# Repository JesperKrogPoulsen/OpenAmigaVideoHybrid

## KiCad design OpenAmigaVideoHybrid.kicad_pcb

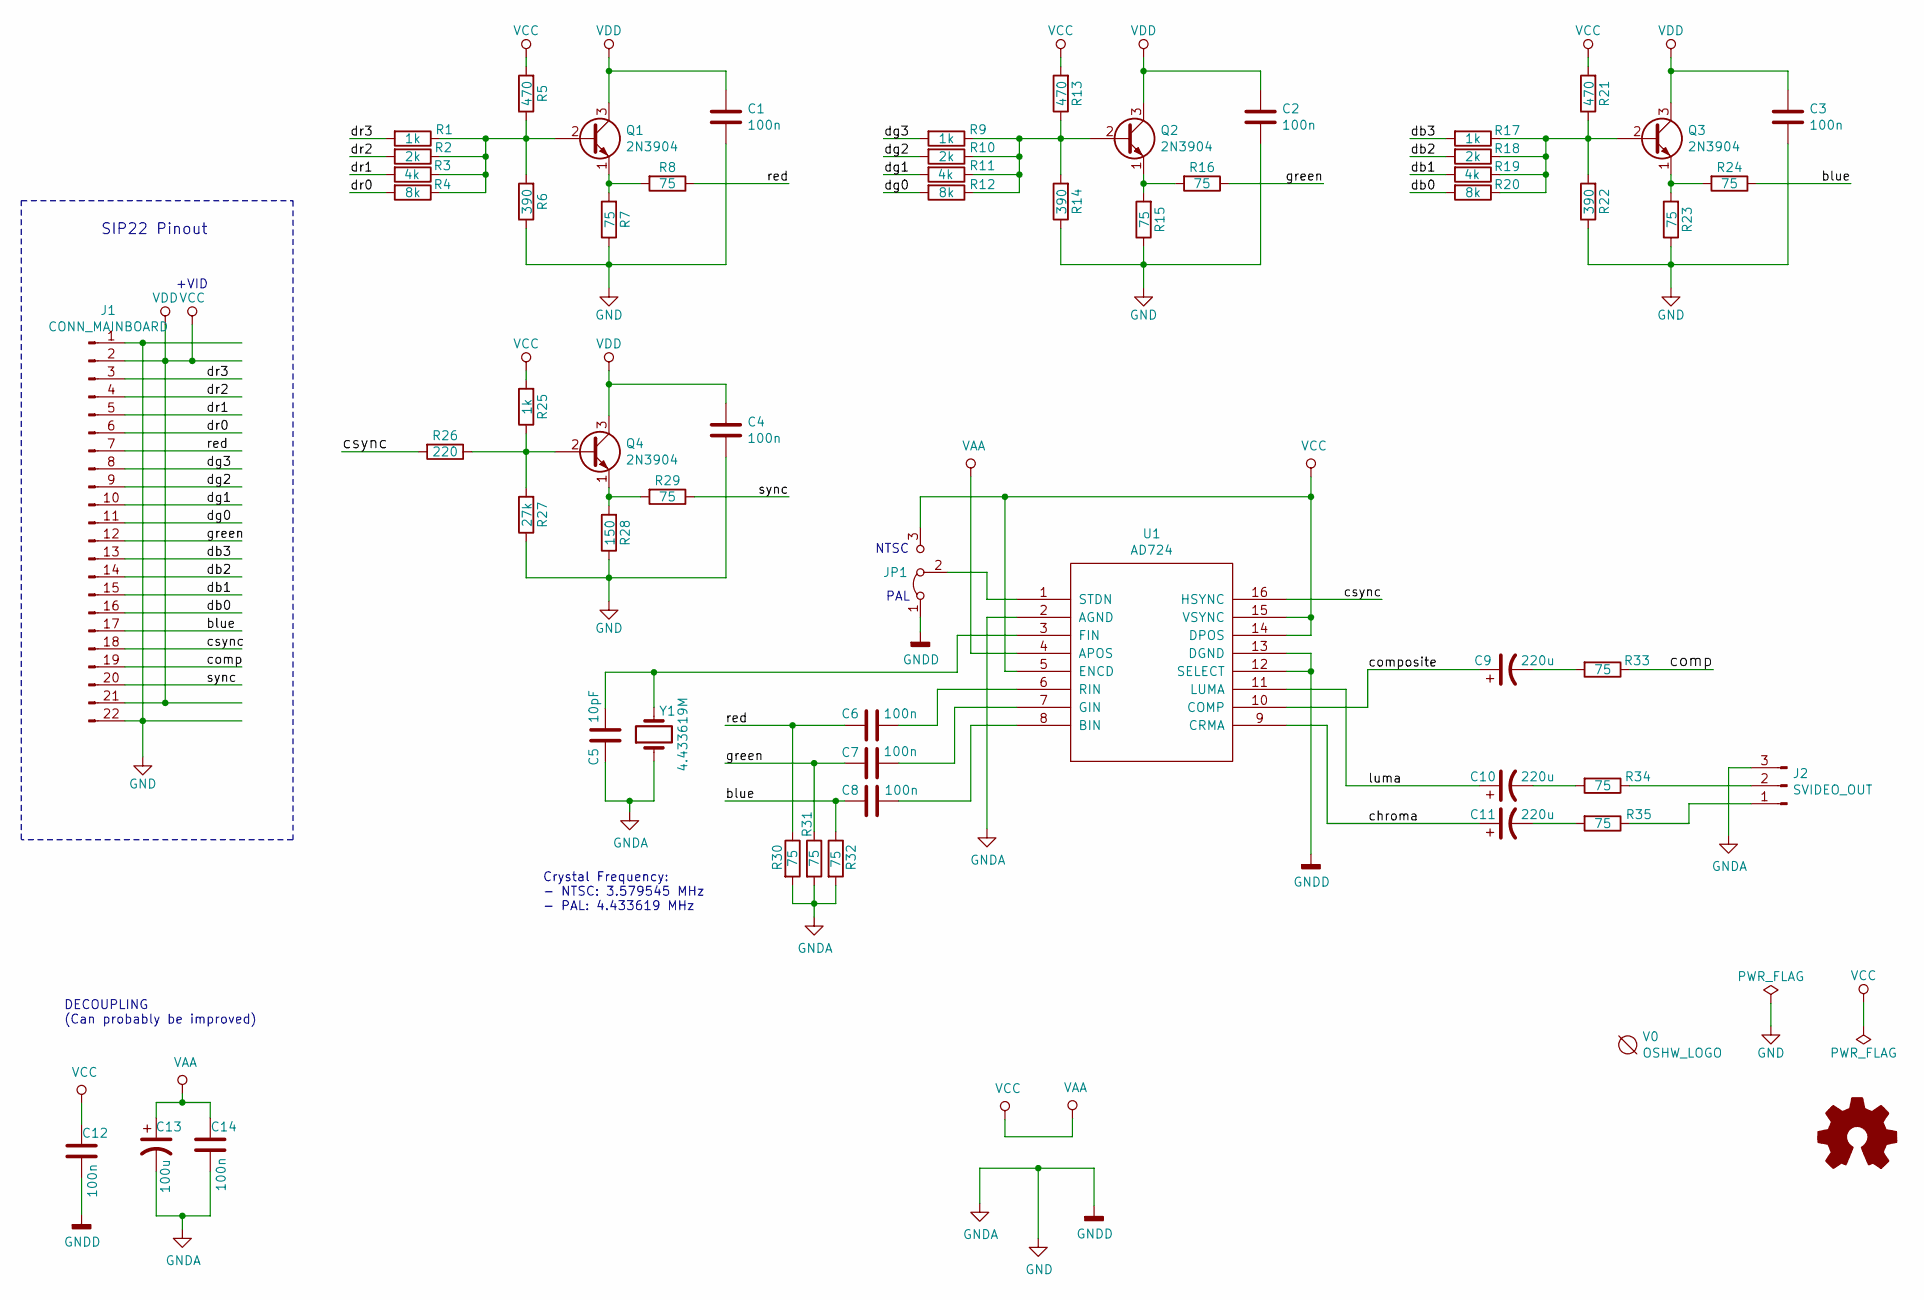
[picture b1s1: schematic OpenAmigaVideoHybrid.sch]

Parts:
C1, C2, C3, C4, C6, C7, C8, C12: 100n; C_0805_2012Metric_Pad1.15x1.40mm_HandSolder
C5: 10pF; C_0805_2012Metric_Pad1.15x1.40mm_HandSolder
C9, C10, C11: 220u; CP_Elec_6.3x7.7
C13: 100u; CP_Elec_6.3x5.8
C14: 100n; C_1206_3216Metric_Pad1.42x1.75mm_HandSolder
J1: CONN_MAINBOARD; PinHeader_1x22_P2.54mm_Vertical
J2: SVIDEO_OUT; Pin_Header_Straight_1x03-ModSilkS
JP1: NTSC/~PAL; SolderJumper-3_P1.3mm_Bridged12_RoundedPad1.0x1.5mm
Q1, Q2, Q3, Q4: 2N3904; 2N3904_2N3906_SOT-23
R1, R9, R17, R25: 1k; R_0805_2012Metric_Pad1.15x1.40mm_HandSolder
R2, R10, R18: 2k; R_0805_2012Metric_Pad1.15x1.40mm_HandSolder
R3, R11, R19: 4k; R_0805_2012Metric_Pad1.15x1.40mm_HandSolder
R4, R12, R20: 8k; R_0805_2012Metric_Pad1.15x1.40mm_HandSolder
R5, R13, R21: 470; R_0805_2012Metric_Pad1.15x1.40mm_HandSolder
R6, R14, R22: 390; R_0805_2012Metric_Pad1.15x1.40mm_HandSolder
R7, R8, R15, R16, R23, R24, R29, R30, R31, R32, R33, R34, R35: 75; R_0805_2012Metric_Pad1.15x1.40mm_HandSolder
R26: 220; R_0805_2012Metric_Pad1.15x1.40mm_HandSolder
R27: 27k; R_0805_2012Metric_Pad1.15x1.40mm_HandSolder
R28: 150; R_0805_2012Metric_Pad1.15x1.40mm_HandSolder
U1: AD724; SOIC-16W_7.5x10.3mm_P1.27mm
V0: OSHW_LOGO; oshw_logo
Y1: 4.433619M; Crystal_SMD_HC49-SD

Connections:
/blue: C8.2, J1.17, R24.1, R32.1
/chroma: C11.1, U1.9 (CRMA)
/comp: J1.19, R33.1
/composite: C9.1, U1.10 (COMP)
/csync: J1.18, R26.2, U1.16 (HSYNC)
/db0: J1.16, R20.2
/db1: J1.15, R19.2
/db2: J1.14, R18.2
/db3: J1.13, R17.2
/dg0: J1.11, R12.2
/dg1: J1.10, R11.2
/dg2: J1.9, R10.2
/dg3: J1.8, R9.2
/dr0: J1.6, R4.2
/dr1: J1.5, R3.2
/dr2: J1.4, R2.2
/dr3: J1.3, R1.2
/green: C7.2, J1.12, R16.1, R31.1
/luma: C10.1, U1.11 (LUMA)
/red: C6.2, J1.7, R8.1, R30.1
/sync: J1.20, R29.1
GND: C1.2, C2.2, C3.2, C4.2, C5.2, C12.1, C13.2, C14.1, J1.1, J1.22, J2.3, JP1.1 (A), R6.1, R7.1, R14.1, R15.1, R22.1, R23.1, R27.1, R28.1, R30.2, R31.2, R32.2, U1.2 (AGND), U1.12 (SELECT), U1.13 (DGND), Y1.1
unnamed: C5.1, U1.3 (FIN), Y1.2
unnamed: C6.1, U1.6 (RIN)
unnamed: C7.1, U1.7 (GIN)
unnamed: C8.1, U1.8 (BIN)
unnamed: C9.2, R33.2
unnamed: C10.2, R34.2
unnamed: C11.2, R35.2
unnamed: J2.1, R35.1
unnamed: J2.2, R34.1
unnamed: JP1.2 (C), U1.1 (STDN)
unnamed: Q1.1 (E), R7.2, R8.2
unnamed: Q1.2 (B), R1.1, R2.1, R3.1, R4.1, R5.1, R6.2
unnamed: Q2.1 (E), R15.2, R16.2
unnamed: Q2.2 (B), R9.1, R10.1, R11.1, R12.1, R13.1, R14.2
unnamed: Q3.1 (E), R23.2, R24.2
unnamed: Q3.2 (B), R17.1, R18.1, R19.1, R20.1, R21.1, R22.2
unnamed: Q4.1 (E), R28.2, R29.2
unnamed: Q4.2 (B), R25.1, R26.1, R27.2
VAA: C1.1, C2.1, C3.1, C4.1, C12.2, C13.1, C14.2, J1.2, J1.21, JP1.3 (B), Q1.3 (C), Q2.3 (C), Q3.3 (C), Q4.3 (C), R5.2, R13.2, R21.2, R25.2, U1.4 (APOS), U1.5 (ENCD), U1.14 (DPOS), U1.15 (VSYNC)

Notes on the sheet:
+VID
SIP22 Pinout
PAL
NTSC
Crystal Frequency: - NTSC: 3.579545 MHz - PAL: 4.433619 MHz
DECOUPLING (Can probably be improved)

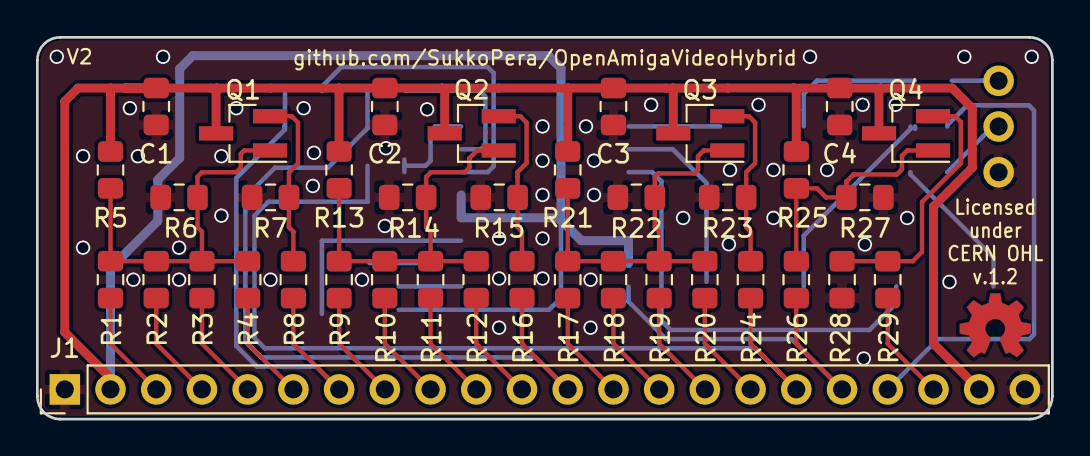
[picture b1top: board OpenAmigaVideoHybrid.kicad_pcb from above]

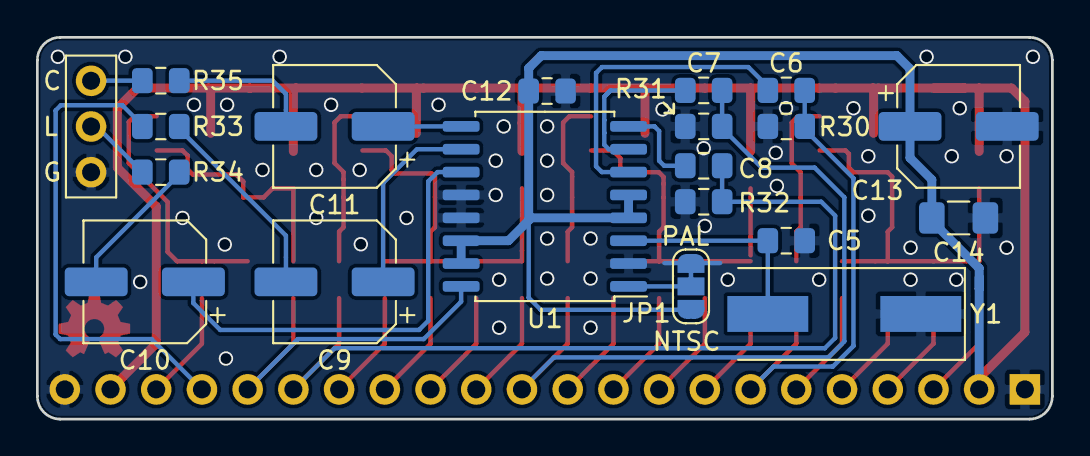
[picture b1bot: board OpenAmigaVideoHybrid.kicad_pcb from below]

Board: 2 copper layers, 56.4 x 21.2 mm, 59 parts (20 on the bottom side), 41 nets.

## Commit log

2020-03-31 Begin migrating project to KiCad 5
2020-03-31 Start working on color composite version
2020-03-31 Almost there...
2020-03-31 Even closer...
2020-03-31 THERE! Just needs some polishing!
2020-04-01 Polish hybrid side
2020-04-01 Getting closer...
2020-04-01 Some more stitching and we're done
2020-04-01 Done!
2020-04-01 Fit schematics to a single A4 sheet
2020-04-01 Fix ERC
2020-04-02 I think we can call this good

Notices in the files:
OpenAmigaVideoHybrid.kicad_pcb:
Licensed under CERN OHL v.1.2
CERN OHL
